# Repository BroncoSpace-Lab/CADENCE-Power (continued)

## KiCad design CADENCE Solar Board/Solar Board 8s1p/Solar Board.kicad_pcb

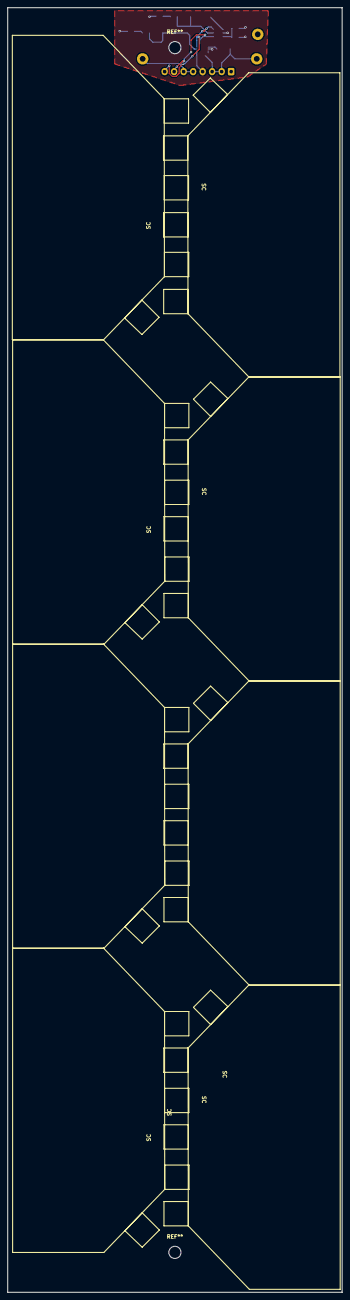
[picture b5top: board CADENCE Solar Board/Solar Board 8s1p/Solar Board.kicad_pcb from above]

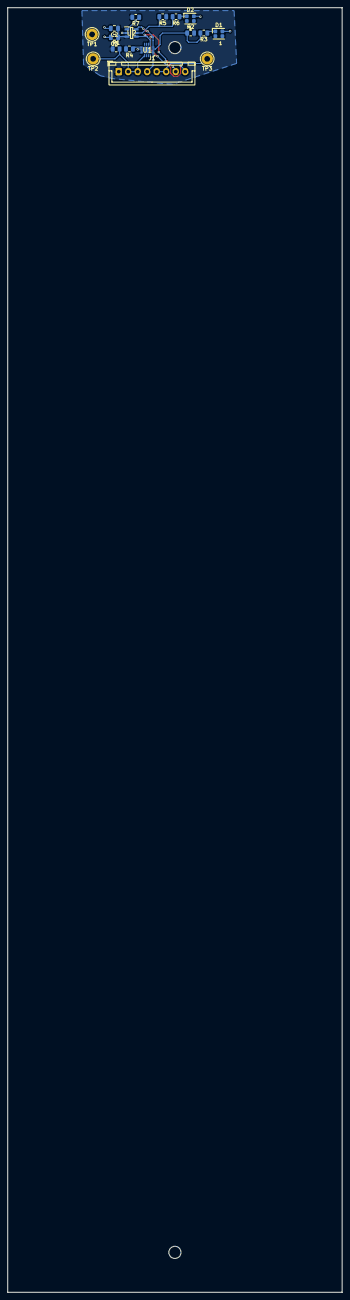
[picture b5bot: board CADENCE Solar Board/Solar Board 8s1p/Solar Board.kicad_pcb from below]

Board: 2 copper layers, 88.0 x 338.0 mm, 25 parts (17 on the bottom side), 12 nets.

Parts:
C2: 10uF; C_0805_2012Metric
C3: 100nF; C_0805_2012Metric
D1, D2: LED; LED_RGB_Lumex_SML-LXT0805SIUGUBW
J1: Conn_01x08; JST_XH_B8B-XH-A_1x08_P2.50mm_Vertical
R1: 0.01; R_0805_2012Metric
R2, R4, R5: 10k; R_0805_2012Metric
R3, R6: 500; R_0805_2012Metric
R7: 1k; R_0805_2012Metric
SC: CAVU Solar Cell
SC#2, SC#3, SC#4, SC#5, SC#6, SC#7, SC#8: CAVU Solar Cell
TP1: Sensor Input; Pin_D1.3mm_L11.0mm_LooseFit
TP2: S1+; Pin_D1.3mm_L11.0mm_LooseFit
TP3: S1-; Pin_D1.3mm_L11.0mm_LooseFit
U1: INA230AIRGTT; QFN50P300X300X100-17N-D
U2: AD7414ARTZ-1REEL7; SOT95P280X145-6N

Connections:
+3.3V: C2.1, C3.1, J1.1, R1.1, R2.2, R4.2, R5.1, R7.2, TP1.1 (1_1), U1.11 (BUS), U1.12 (IN-), U2.3 (VDD)
GND: C2.2, C3.2, D1.1 (K), D2.1 (K), J1.4, U1.1 (A1), U1.2 (A0), U1.10 (GND), U2.2 (GND)
HS_I2C1_LCL: J1.7, U1.5 (SCL), U2.4 (SCL)
HS_I2C1_LDA: J1.8, U1.4 (SDA), U2.6 (SDA)
unnamed: D1.2 (A), R3.1
unnamed: D2.2 (A), R6.1
unnamed: R2.1, R3.2, U1.3 (ALERT)
unnamed: R4.1, U1.9 (V_S+)
unnamed: R5.2, R6.2, U2.5 (ALERT)
unnamed: R7.1, U2.1 (AS)
Solar1+: J1.2, J1.3, R1.2, TP2.1 (1_1), U1.13 (IN+)
Solar1-: J1.5, J1.6, TP3.1 (1_1)
